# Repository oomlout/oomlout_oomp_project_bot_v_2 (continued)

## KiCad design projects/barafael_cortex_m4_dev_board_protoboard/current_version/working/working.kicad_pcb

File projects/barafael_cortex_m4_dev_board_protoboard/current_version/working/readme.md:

# cortex_m4_dev_board
 
## summary 
* id: barafael_cortex_m4_dev_board_protoboard
* user: barafael
* name: cortex_m4_dev_board
* board: protoboard
* repo: https://github.com/barafael/cortex-m4-dev-board
* src_file_repo_kicad_pcb: protoboard/protoboard.kicad_pcb
* src_file_repo_kicad_pcb_link: https://github.com/barafael/cortex-m4-dev-board/tree/master/protoboard/protoboard.kicad_pcb

* src_file_repo_sch: 
* src_file_repo_sch_link: https://github.com/barafael/cortex-m4-dev-board/tree/master/
* full details link: https://github.com/oomlout/oomlout_oomp_project_bot_v_2/tree/main/projects/barafael_cortex_m4_dev_board_protoboard/current_version/working

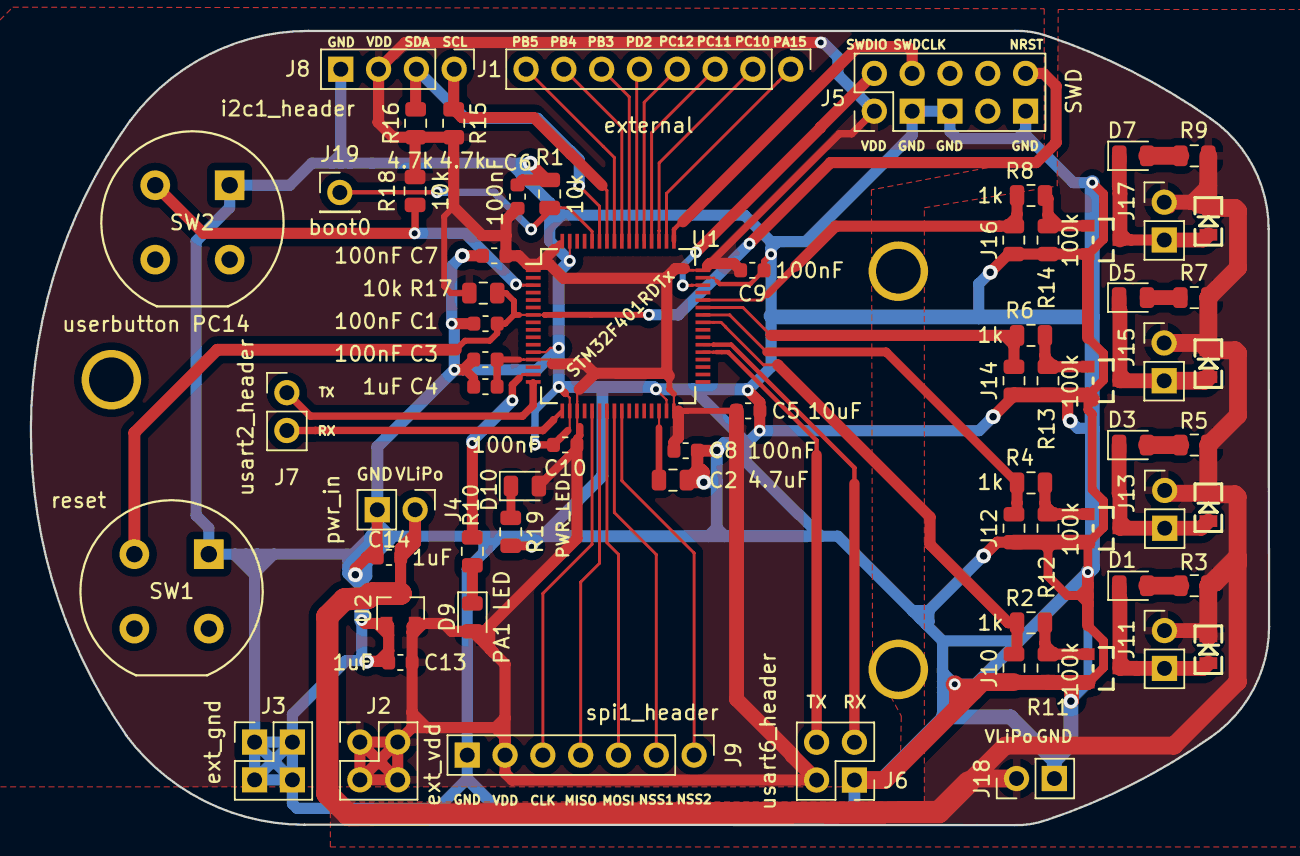
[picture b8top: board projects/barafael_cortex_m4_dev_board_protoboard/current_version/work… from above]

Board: 2 copper layers, 83.2 x 53.4 mm, 71 parts (0 on the bottom side), 47 nets.

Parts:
1pin_prototyping, 1pin_prototyping#2, 1pin_prototyping#3: val**; 1pin_prototyping
C1, C3, C6, C7, C8, C9, C10: 100nF; C_0603_1608Metric
C2: 4.7uF; C_0805_2012Metric
C4, C13, C14: 1uF; C_0603_1608Metric
C5: 10uF; C_0603_1608Metric
D1, D3, D5, D7: LED; LED_0805_2012Metric
D2, D4, D6, D8: DIODE; LED-0805
D9: PA1 LED; LED_0805_2012Metric
D10: PWR_LED; LED_0805_2012Metric
J1: external; PinHeader_1x08_P2.54mm_Vertical
J2: ext_vdd; PinHeader_2x02_P2.54mm_Vertical
J3: ext_gnd; PinHeader_2x02_P2.54mm_Vertical
J4, J18: pwr_in; PinHeader_1x02_P2.54mm_Vertical
J5: SWD; PinHeader_2x05_P2.54mm_Vertical
J6: usart6_header; PinHeader_2x02_P2.54mm_Vertical
J7: usart2_header; PinHeader_1x02_P2.54mm_Vertical
J8: i2c1_header; PinHeader_1x04_P2.54mm_Vertical
J9: spi1_header; PinHeader_1x07_P2.54mm_Vertical
J10, J12, J14, J16: Conn_01x02_Female; R_0805_2012Metric
J11, J13, J15, J17: brushed_out; PinHeader_1x02_P2.54mm_Vertical
J19: boot0; PinHeader_1x01_P2.54mm_Vertical
Q1, Q2, Q3, Q4: MOSFET_N; SOT23_FET
R1, R17, R18: 10k; R_0805_2012Metric
R2, R4, R6, R8: 1k; R_0805_2012Metric
R3, R5, R7, R9, R10, R19: 500; R_0805_2012Metric
R11, R12, R13, R14: 100k; R_0805_2012Metric
R15, R16: 4.7k; R_0805_2012Metric
SW1: reset; Push_E-Switch_KS01Q01
SW2: userbutton PC14; Push_E-Switch_KS01Q01
U1: STM32F401RDTx; LQFP-64_10x10mm_P0.5mm
U2: MCP1700-3302E_TO92; mcp1700

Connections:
GND: C1.2, C2.2, C3.2, C4.2, C5.2, C6.2, C7.2, C8.2, C9.2, C10.2, C13.2, C14.2, J3.1, J3.2, J3.3, J3.4, J4.2, J5.3, J5.5, J5.9, J6.1, J8.4, J9.7, J10.1, J12.1, J14.1, J16.1, J18.2, Q1.S, Q2.S, Q3.S, Q4.S, R1.2, R11.1, R12.1, R13.1, R14.1, R19.2, SW1.2, SW2.2, U1.12, U1.18, U1.31, U1.47, U1.63, U2.1
I2C1_SCL: J8.1, R15.1, U1.58
I2C1_SDA: J8.2, R16.2, U1.59
NRST: C1.1, J5.10, R17.2, SW1.1, U1.7
unnamed: D1.1, D2.A, J11.2, Q1.D
unnamed: D1.2, R3.2
unnamed: D3.1, D4.A, J13.2, Q2.D
unnamed: D3.2, R5.2
unnamed: D5.1, D6.A, J15.2, Q3.D
unnamed: D5.2, R7.2
unnamed: D7.1, D8.A, J17.2, Q4.D
unnamed: D7.2, R9.2
unnamed: D9.1, R10.1
unnamed: D10.1, R19.1
unnamed: Q1.G, R2.1, R11.2
unnamed: Q2.G, R4.1, R12.2
unnamed: Q3.G, R6.1, R13.2
unnamed: Q4.G, R8.1, R14.2
PA15: J1.1, U1.50
PB3: J1.6, U1.55
PB4: J1.7, U1.56
PB5: J1.8, U1.57
PC10: J1.2, U1.51
PC11: J1.3, U1.52
PC12: J1.4, U1.53
PD2: J1.5, U1.54
PWM1: J10.2, R2.2, U1.41
PWM2: J12.2, R4.2, U1.42
PWM3: J14.2, R6.2, U1.43
PWM4: J16.2, R8.2, U1.44
SPI1CLK: J9.5, U1.21
SPI1MISO: J9.4, U1.22
SPI1MOSI: J9.3, U1.23
SPI1NSS1: J9.2, U1.24
SPI1NSS2: J9.1, U1.25
SWDCLK: J5.4, U1.49
SWDIO: J5.2, U1.46
USART2_RX: J7.2, U1.17
USART2_TX: J7.1, U1.16
USART6_RX: J6.3, U1.38
USART6_TX: J6.4, U1.37
VDD: C3.1, C4.1, C5.1, C6.1, C7.1, C8.1, C9.1, C10.1, C13.1, D9.2, D10.2, J2.1, J2.2, J2.3, J2.4, J5.1, J6.2, J8.3, J9.6, R15.2, R16.1, R17.1, R18.1, U1.1, U1.13, U1.19, U1.32, U1.48, U1.64, U2.3
VLiPo: C14.1, D2.K, D4.K, D6.K, D8.K, J4.1, J11.1, J13.1, J15.1, J17.1, J18.1, R3.1, R5.1, R7.1, R9.1, U2.2
boot0: J19.1, R1.1, U1.60
user_button: R18.2, SW2.1, U1.3
user_led: R10.2, U1.15
vcap1: C2.1, U1.30
